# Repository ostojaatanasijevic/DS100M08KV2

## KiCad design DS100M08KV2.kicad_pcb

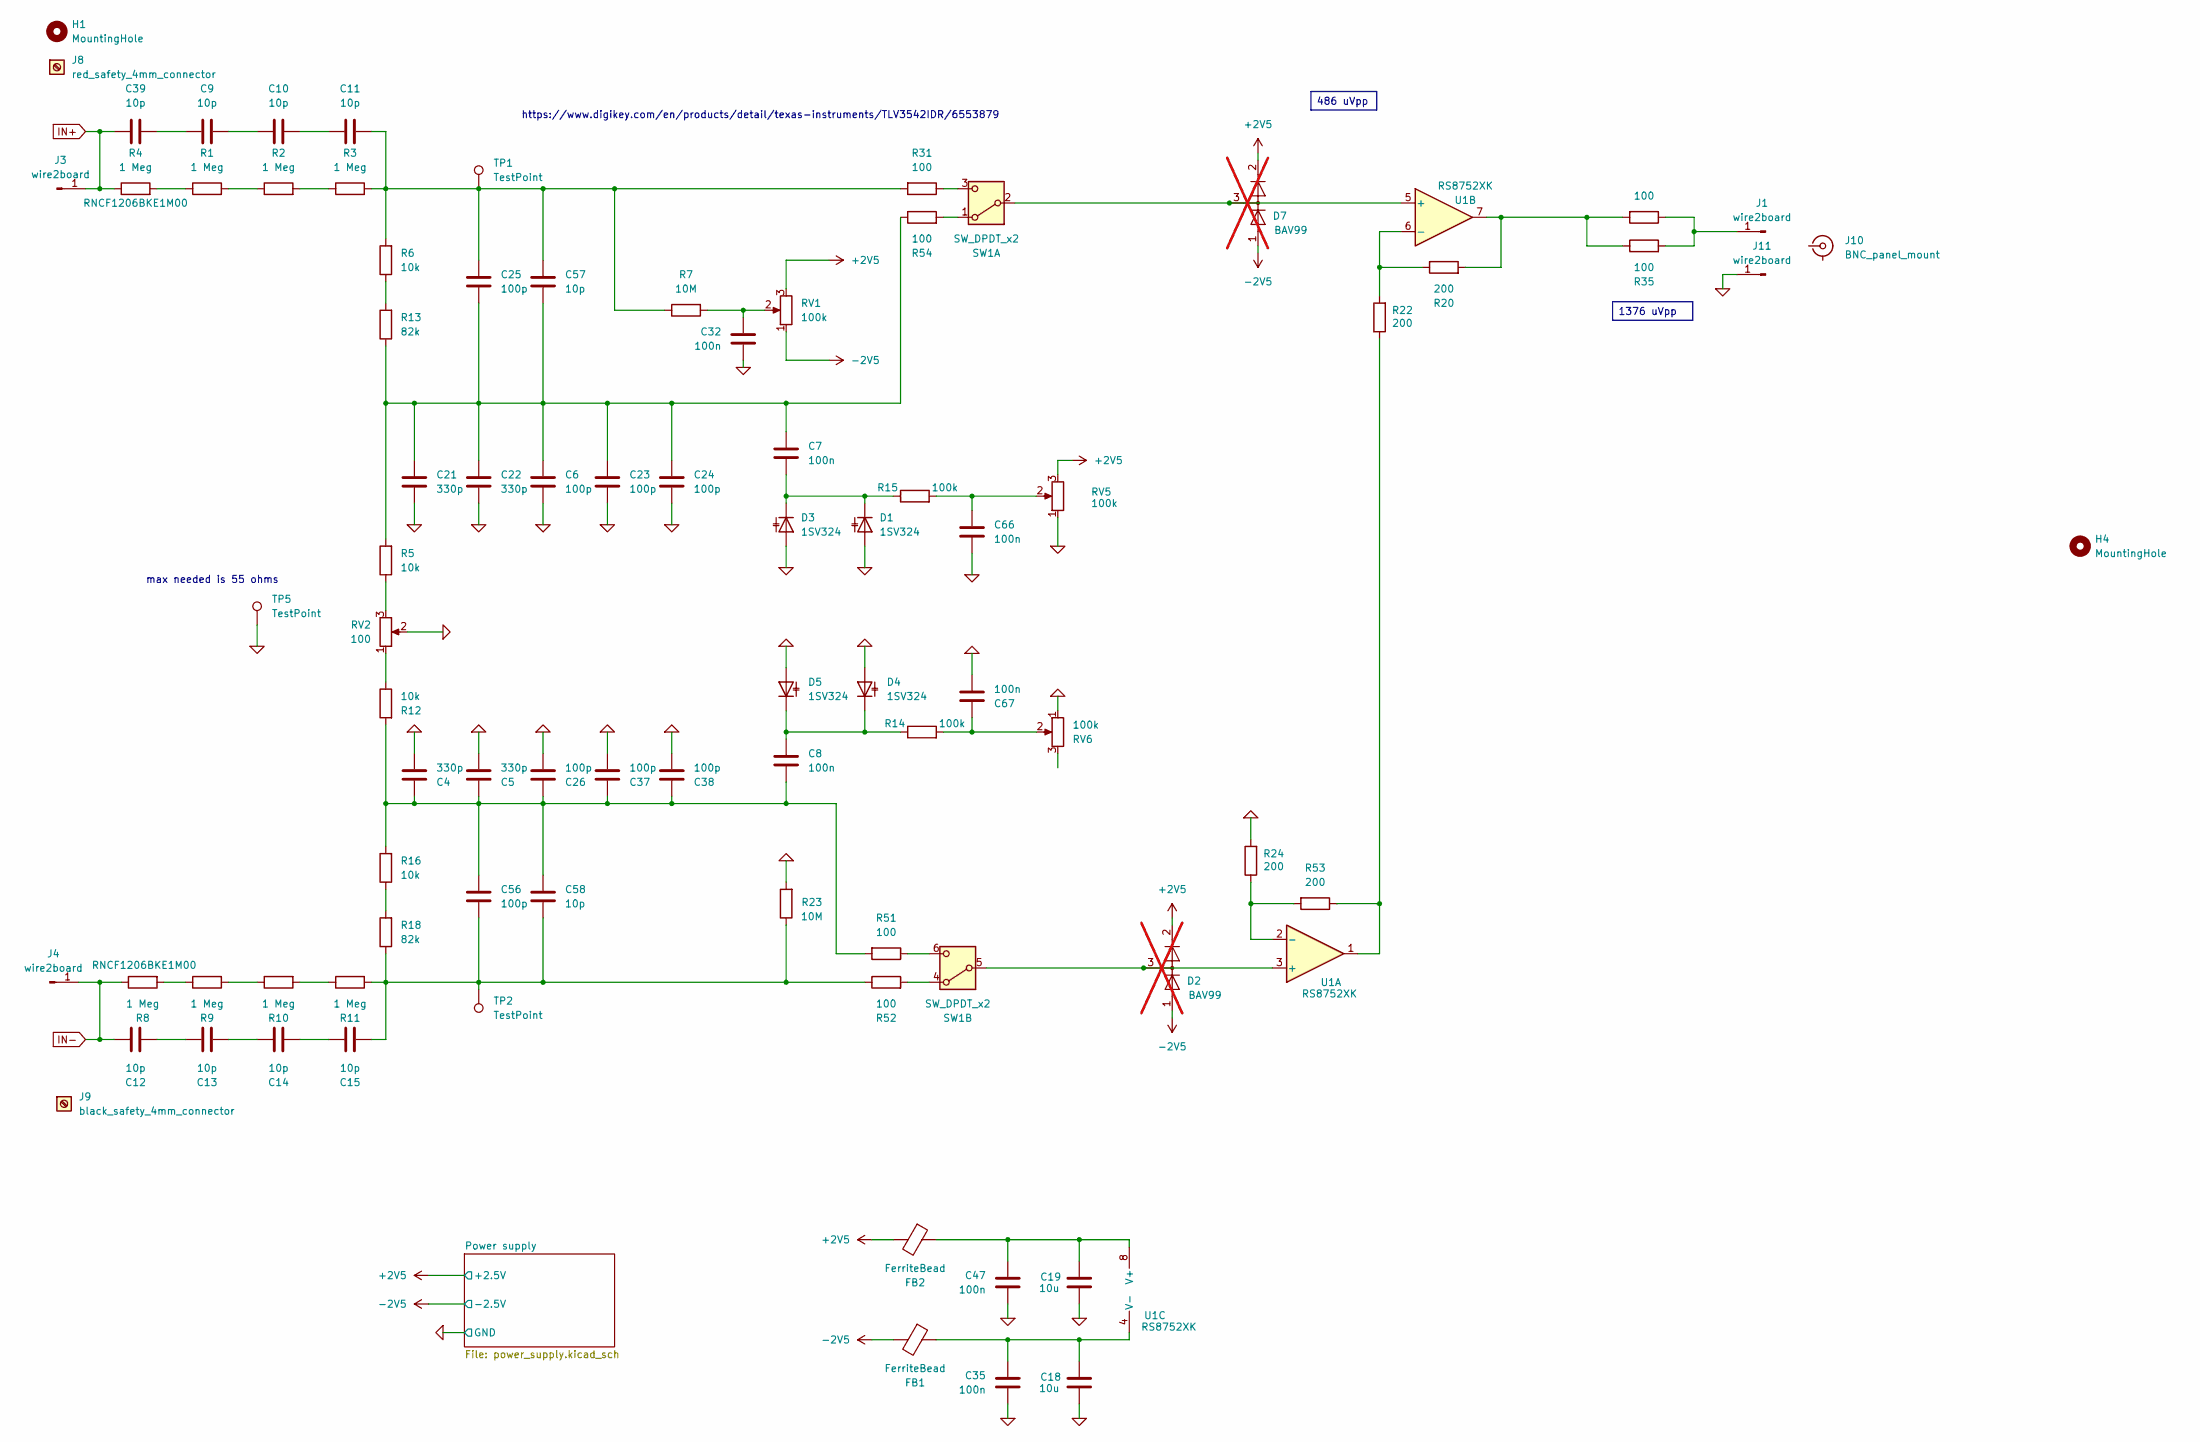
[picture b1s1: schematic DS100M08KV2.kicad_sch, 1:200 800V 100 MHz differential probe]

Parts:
C4, C5, C21, C22: 330p; R_0603_1608Metric_Pad0.98x0.95mm_HandSolder; LCSC C1664
C6, C23, C24, C25, C26, C37, C38, C56: 100p; R_0603_1608Metric_Pad0.98x0.95mm_HandSolder; LCSC C14858
C7, C8, C32, C35, C47, C66, C67: 100n; C_0603_1608Metric_Pad1.08x0.95mm_HandSolder; LCSC C14663
C9, C10, C11, C12, C13, C14, C15, C39: 10p; R_1206_3216Metric_Pad1.30x1.75mm_HandSolder
C18, C19: 10u; C_0603_1608Metric_Pad1.08x0.95mm_HandSolder; LCSC C96446
C57, C58: 10p; R_0603_1608Metric_Pad0.98x0.95mm_HandSolder; LCSC C1634
D1, D3, D4, D5: 1SV324; D_SOD-323_HandSoldering
D2, D7: BAV99; SOT-23; LCSC C2500; not fitted
FB1, FB2: FerriteBead; L_0603_1608Metric_Pad1.05x0.95mm_HandSolder
H1, H4: MountingHole; M3_with_screw
J1, J3, J4, J11: wire2board; SolderWire-0.25sqmm_1x01_D0.65mm_OD1.7mm
J8: red_safety_4mm_connector; black_safety_4mm_connector
J9: black_safety_4mm_connector
J10: BNC_panel_mount
R1, R2, R3, R9, R10, R11: 1 Meg; R_1206_3216Metric_Pad1.30x1.75mm_HandSolder
R4, R8: 1 Meg; R_1206_3216Metric_Pad1.30x1.75mm_HandSolder; Partnumber RNCF1206BKE1M00
R5, R6, R12, R16: 10k; R_0603_1608Metric_Pad0.98x0.95mm_HandSolder
R7, R23: 10M; R_0603_1608Metric_Pad0.98x0.95mm_HandSolder; LCSC C7250
R13, R18: 82k; R_0603_1608Metric_Pad0.98x0.95mm_HandSolder
R14, R15: 100k; R_0603_1608Metric_Pad0.98x0.95mm_HandSolder; LCSC C25803
R17, R31, R35, R51, R52, R54: 100; R_0603_1608Metric_Pad0.98x0.95mm_HandSolder; LCSC C22775
R20, R22, R24, R53: 200; R_0603_1608Metric_Pad0.98x0.95mm_HandSolder
RV1, RV5, RV6: 100k; Potentiometer_Bourns_3296W_Vertical
RV2: 100; Potentiometer_Bourns_3296W_Vertical
SW1: SW_DPDT_x2; DPDT_bigger
TP1, TP2, TP5: TestPoint; TestPoint_Pad_D2.0mm
U1: RS8752XK; SOIC-8_3.9x4.9mm_P1.27mm; LCSC RS8752XK

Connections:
0: C4.2, C5.2, C6.1, C18.2, C19.2, C21.2, C22.2, C23.1, C24.1, C26.1, C32.1, C35.1, C37.1, C38.1, C47.1, C66.1, C67.1, D1.2 (A), D3.2 (A), D4.2 (A), D5.2 (A), J11.1, R23.2, R24.2, RV2.2, RV5.1, RV6.1, TP5.1; also elsewhere on the board
+2V5: D2.2 (A), D7.2 (A), FB2.2, RV1.3, RV5.3; also elsewhere on the board
-2V5: D2.1 (K), D7.1 (K), FB1.2, RV1.1; also elsewhere on the board
IN+: C39.2, J3.1, R4.1
IN-: C12.2, J4.1, R8.1
unnamed: C10.1, C11.2
unnamed: C9.1, C10.2
unnamed: C11.1, C25.2, C57.2, R3.2, R6.2, R7.1, R31.2, TP1.1
unnamed: C12.1, C13.2
unnamed: C13.1, C14.2
unnamed: C14.1, C15.2
unnamed: C15.1, C56.1, C58.1, R11.2, R18.1, R23.1, R52.1, TP2.1
unnamed: C6.2, C7.2, C21.1, C22.1, C23.2, C24.2, C25.1, C57.1, R5.2, R13.1, R54.1
unnamed: C4.1, C5.1, C8.1, C26.2, C37.2, C38.2, C56.2, C58.2, R12.2, R16.2, R51.2
unnamed: C32.2, R7.2, RV1.2
unnamed: C9.2, C39.1
unnamed: C66.2, R15.2, RV5.2
unnamed: C67.2, R14.2, RV6.2
unnamed: C7.1, D1.1 (K), D3.1 (K), R15.1
unnamed: C8.2, D4.1 (K), D5.1 (K), R14.1
unnamed: J1.1, R17.1, R35.2
unnamed: R1.1, R4.2
unnamed: R1.2, R2.1
unnamed: R2.2, R3.1
unnamed: R5.1, RV2.3
unnamed: R8.2, R9.1
unnamed: R9.2, R10.1
unnamed: R10.2, R11.1
unnamed: R12.1, RV2.1
unnamed: R6.1, R13.2
unnamed: R16.1, R18.2
unnamed: R17.2, R20.2, R35.1, U1.7
unnamed: R22.1, R53.1, U1.1
unnamed: R54.2, SW1.1 (A)
unnamed: D7.3 (K), SW1.2 (B), U1.5 (+)
unnamed: R31.1, SW1.3 (C)
unnamed: R52.2, SW1.4 (A)
unnamed: D2.3 (K), SW1.5 (B), U1.3 (+)
unnamed: R51.1, SW1.6 (C)
unnamed: R24.1, R53.2, U1.2 (-)
unnamed: R20.1, R22.2, U1.6 (-)
unnamed: C19.1, C47.2, FB2.1, U1.8 (V+)
unnamed: C18.1, C35.2, FB1.1, U1.4 (V-)

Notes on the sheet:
https://www.digikey.com/en/products/detail/texas-instruments/TLV3542IDR/6553879
max needed is 55 ohms
1376 uVpp
486 uVpp

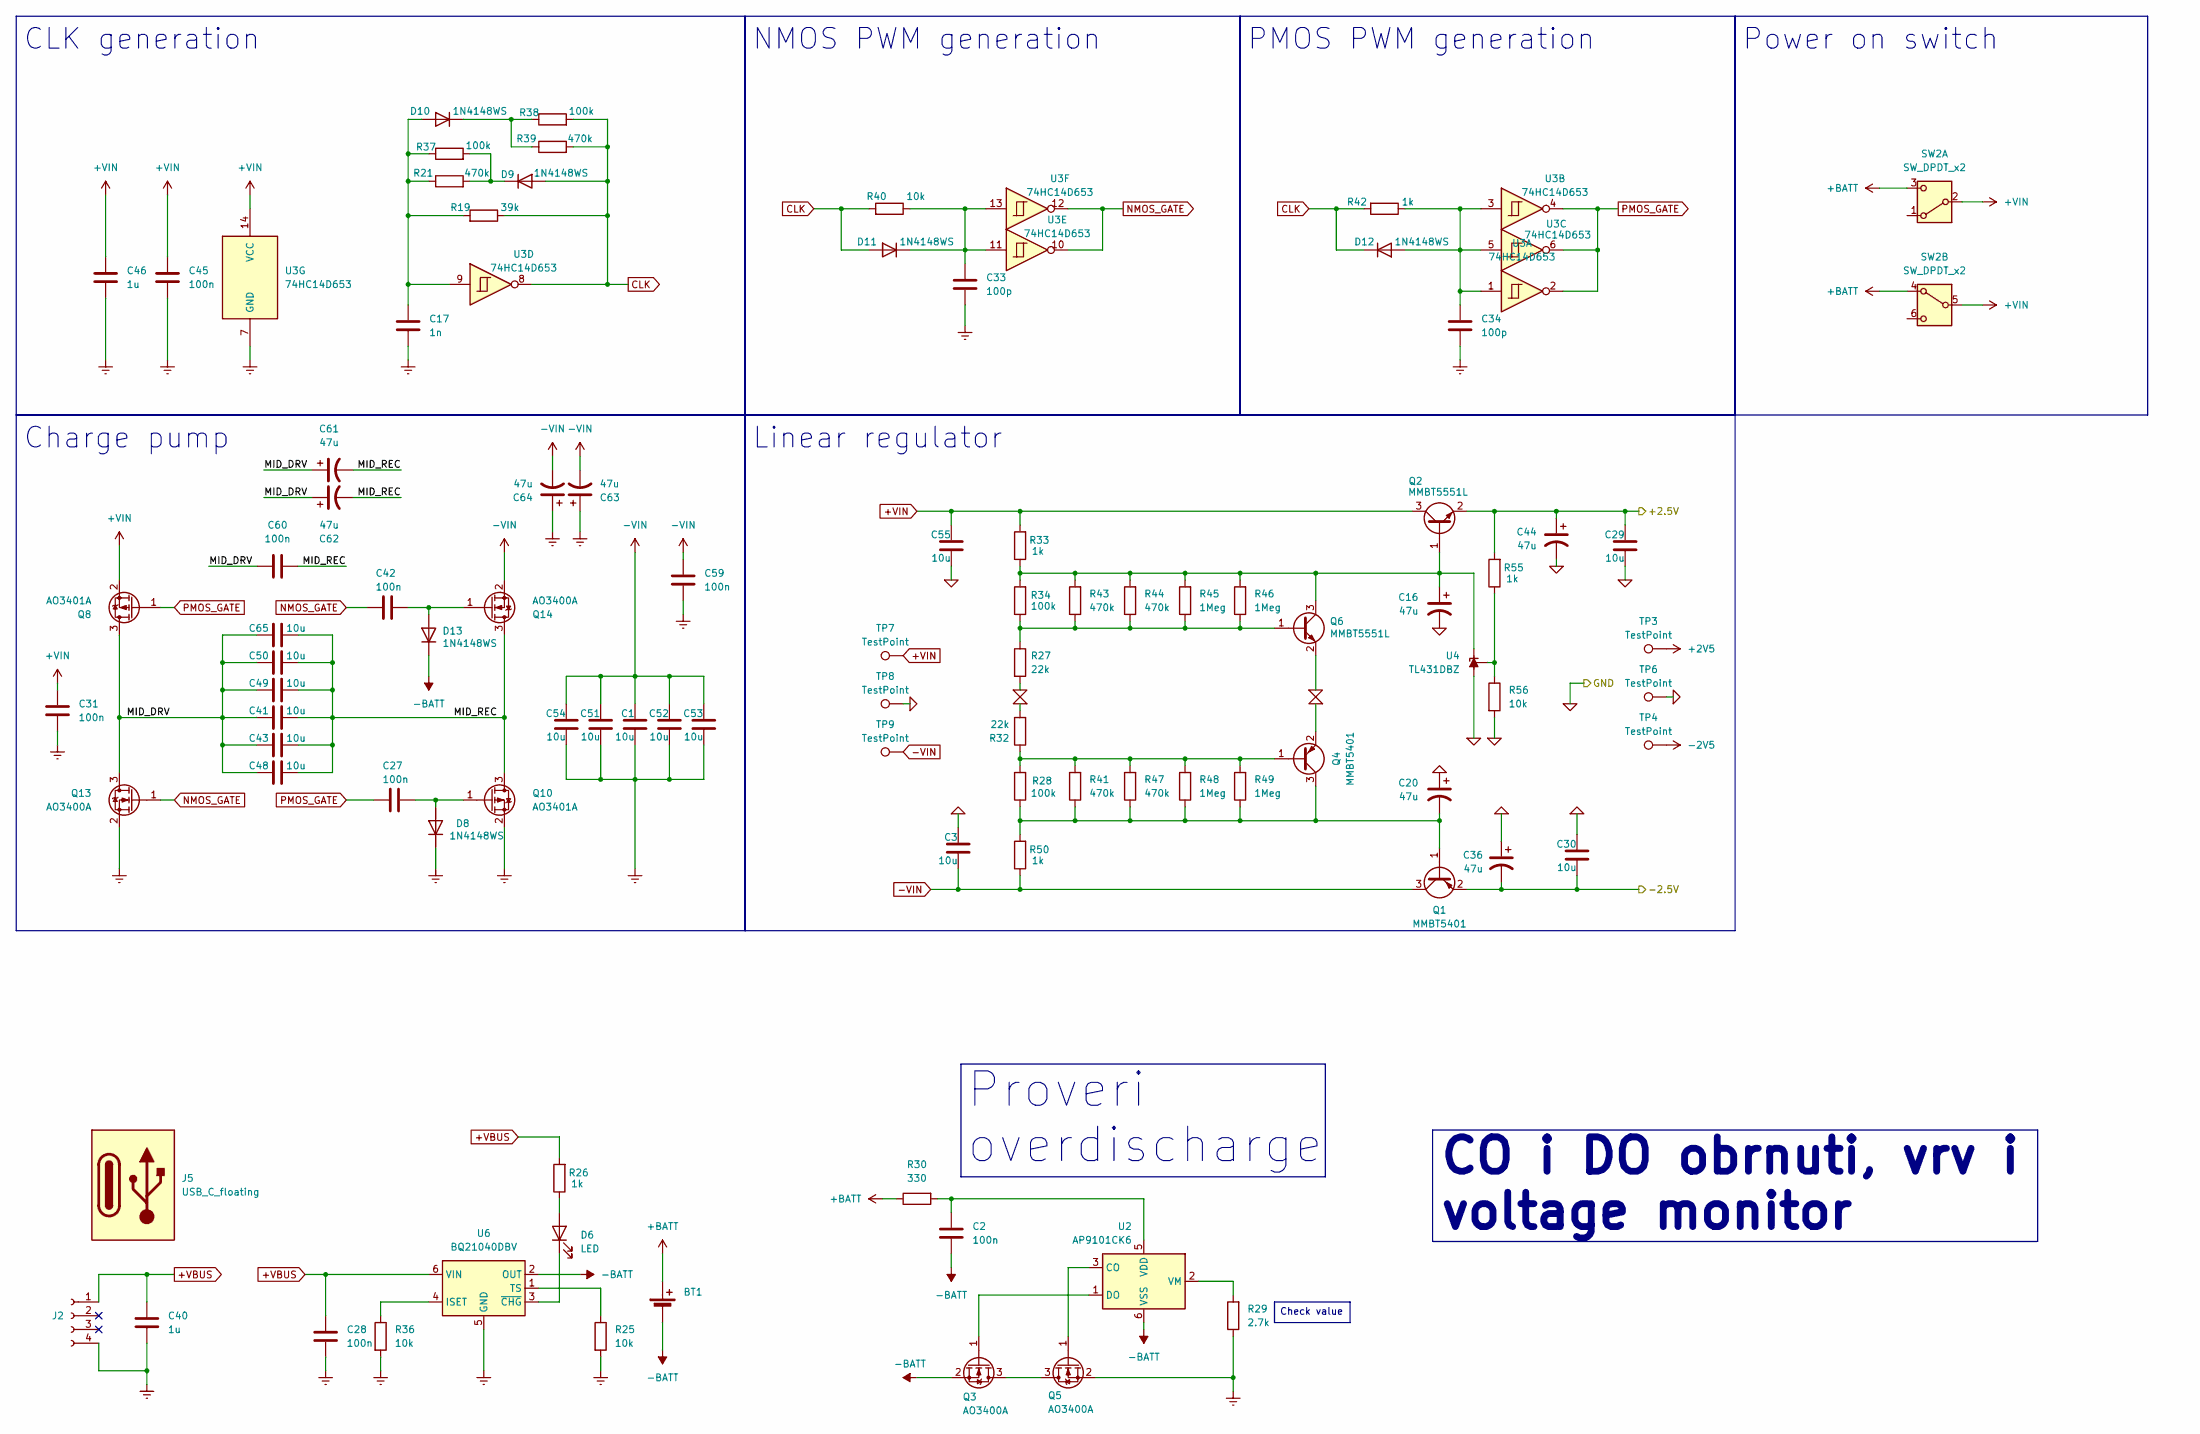
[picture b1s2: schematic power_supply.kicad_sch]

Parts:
BT1: Battery_Cell; battery_holder
C1, C3, C29, C30, C41, C43, C48, C49, C50, C51, C52, C53, C54, C55, C65: 10u; R_0805_2012Metric_Pad1.20x1.40mm_HandSolder; Voltage 25V; LCSC C15850
C2, C27, C28, C31, C42, C45, C59, C60: 100n; C_0603_1608Metric_Pad1.08x0.95mm_HandSolder; LCSC C14663
C16, C20, C36, C44, C61, C62, C63, C64: 47u; CP_Radial_D5.0mm_P2.00mm
C17: 1n; C_0603_1608Metric_Pad1.08x0.95mm_HandSolder; LCSC C1588
C33, C34: 100p; C_0603_1608Metric_Pad1.08x0.95mm_HandSolder; LCSC C14858
C40, C46: 1u; C_0603_1608Metric_Pad1.08x0.95mm_HandSolder; LCSC C15849
D6: LED; LED_D3.0mm_FlatTop
D8, D9, D10, D11, D12, D13: 1N4148WS; D_SOD-323; LCSC C2128
J2: Conn_01x04_Socket; JST_PH_B4B-PH-K_1x04_P2.00mm_Vertical
J5: USB_C_floating
Q1, Q4: MMBT5401; SOT-23; LCSC C8326
Q2, Q6: MMBT5551L; SOT-23; LCSC C2145
Q3, Q5, Q13, Q14: AO3400A; SOT-23; LCSC C20917
Q8, Q10: AO3401A; SOT-23; LCSC C15127
R19: 39k; R_0603_1608Metric_Pad0.98x0.95mm_HandSolder; LCSC C23153
R21, R39, R41, R43, R44, R47: 470k; R_0603_1608Metric_Pad0.98x0.95mm_HandSolder; LCSC C23178
R25, R36, R40, R56: 10k; R_0603_1608Metric_Pad0.98x0.95mm_HandSolder; LCSC C25804
R26, R33, R42, R50, R55: 1k; R_0603_1608Metric_Pad0.98x0.95mm_HandSolder; LCSC C21190
R27, R32: 22k; R_0603_1608Metric_Pad0.98x0.95mm_HandSolder; LCSC C31850
R28, R34, R37, R38: 100k; R_0603_1608Metric_Pad0.98x0.95mm_HandSolder; LCSC C25803
R29: 2.7k; R_0603_1608Metric_Pad0.98x0.95mm_HandSolder; LCSC C13167
R30: 330; R_0603_1608Metric_Pad0.98x0.95mm_HandSolder; LCSC C23138
R45, R46, R48, R49: 1Meg; R_0603_1608Metric_Pad0.98x0.95mm_HandSolder; LCSC C22935
SW2: SW_DPDT_x2; DPDT_bigger
TP3, TP4, TP6, TP7, TP8, TP9: TestPoint; TestPoint_Pad_D2.0mm
U2: AP9101CK6; SOT-23-6
U3: 74HC14D653; SOIC-14_3.9x8.7mm_P1.27mm; LCSC C5605
U4: TL431DBZ; SOT-23; LCSC C3113
U6: BQ21040DBV; SOT-23-6

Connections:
0: C3.2, C16.2, C20.1, C29.1, C30.2, C36.1, C44.2, C55.1, Q4.2 (E), Q6.2 (E), R27.2, R32.2, R56.2, TP6.1, TP8.1, U4.3 (A); also elsewhere on the board
+2V5: C29.2, C44.1, Q2.2 (E), R55.2, TP3.1; also elsewhere on the board
+BATT: BT1.1 (+), R30.1, SW2.3 (C), SW2.4 (A)
+VBUS: C28.2, C40.2, J2.1, R26.2, U6.6 (VIN)
+VIN: C31.2, C45.2, C46.2, C55.2, Q2.3 (C), Q8.2 (S), R33.2, SW2.2 (B), SW2.5 (B), TP7.1, U3.14 (VCC)
-2V5: C30.1, C36.2, Q1.2 (E), TP4.1; also elsewhere on the board
-BATT: BT1.2 (-), C2.1, D13.1 (K), Q3.2 (S), U2.6 (VSS), U6.2 (OUT)
-VIN: C1.2, C3.1, C51.2, C52.2, C53.2, C54.2, C59.2, C63.2, C64.2, Q1.3 (C), Q14.2 (S), R50.1, TP9.1
/Power supply/MID_DRV: C41.1, C43.1, C48.1, C49.1, C50.1, C60.2, C61.1, C62.1, C65.1, Q8.3 (D), Q13.3 (D)
/Power supply/MID_REC: C41.2, C43.2, C48.2, C49.2, C50.2, C60.1, C61.2, C62.2, C65.2, Q10.3 (D), Q14.3 (D)
CLK: D9.2 (A), D11.2 (A), D12.1 (K), R19.1, R38.2, R39.2, R40.2, R42.2, U3.8
Earth: C1.1, C17.1, C28.1, C31.1, C33.1, C34.1, C40.1, C45.1, C46.1, C51.1, C52.1, C53.1, C54.1, C59.1, C63.1, C64.1, D8.1 (K), J2.4, Q5.2 (S), Q10.2 (S), Q13.2 (S), R25.2, R29.1, R36.2, U3.7 (GND), U6.5 (GND)
NMOS_GATE: C42.1, Q13.1 (G), U3.10, U3.12
unnamed: D6.2 (A), R26.1
unnamed: D6.1 (K), U6.3 (~CHG)
unnamed: C27.2, D8.2 (A), Q10.1 (G)
unnamed: D9.1 (K), R21.2, R37.2
unnamed: C17.2, D10.2 (A), R19.2, R21.1, R37.1, U3.9
unnamed: D10.1 (K), R38.1, R39.1
unnamed: C33.2, D11.1 (K), R40.1, U3.11, U3.13
unnamed: C34.2, D12.2 (A), R42.1, U3.1, U3.3, U3.5
unnamed: C42.2, D13.2 (A), Q14.1 (G)
unnamed: C20.2, Q1.1 (B), Q4.3 (C), R28.1, R41.1, R47.1, R48.1, R49.1, R50.2
unnamed: C16.1, Q2.1 (B), Q6.3 (C), R33.1, R34.2, R43.2, R44.2, R45.2, R46.2, U4.1 (K)
unnamed: Q3.3 (D), Q5.3 (D)
unnamed: Q3.1 (G), U2.1 (DO)
unnamed: Q4.1 (B), R28.2, R32.1, R41.2, R47.2, R48.2, R49.2
unnamed: Q5.1 (G), U2.3 (CO)
unnamed: Q6.1 (B), R27.1, R34.1, R43.1, R44.1, R45.1, R46.1
unnamed: C2.2, R30.2, U2.5 (VDD)
unnamed: R29.2, U2.2 (VM)
unnamed: R55.1, R56.1, U4.2 (REF)
unnamed: R36.1, U6.4 (ISET)
unnamed: R25.1, U6.1 (TS)
PMOS_GATE: C27.1, Q8.1 (G), U3.2, U3.4, U3.6

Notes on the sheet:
Charge pump
CLK generation
Power on switch
Linear regulator
PMOS PWM generation
NMOS PWM generation
Proveri overdischarge
Check value
CO i DO obrnuti, vrv i voltage monitor

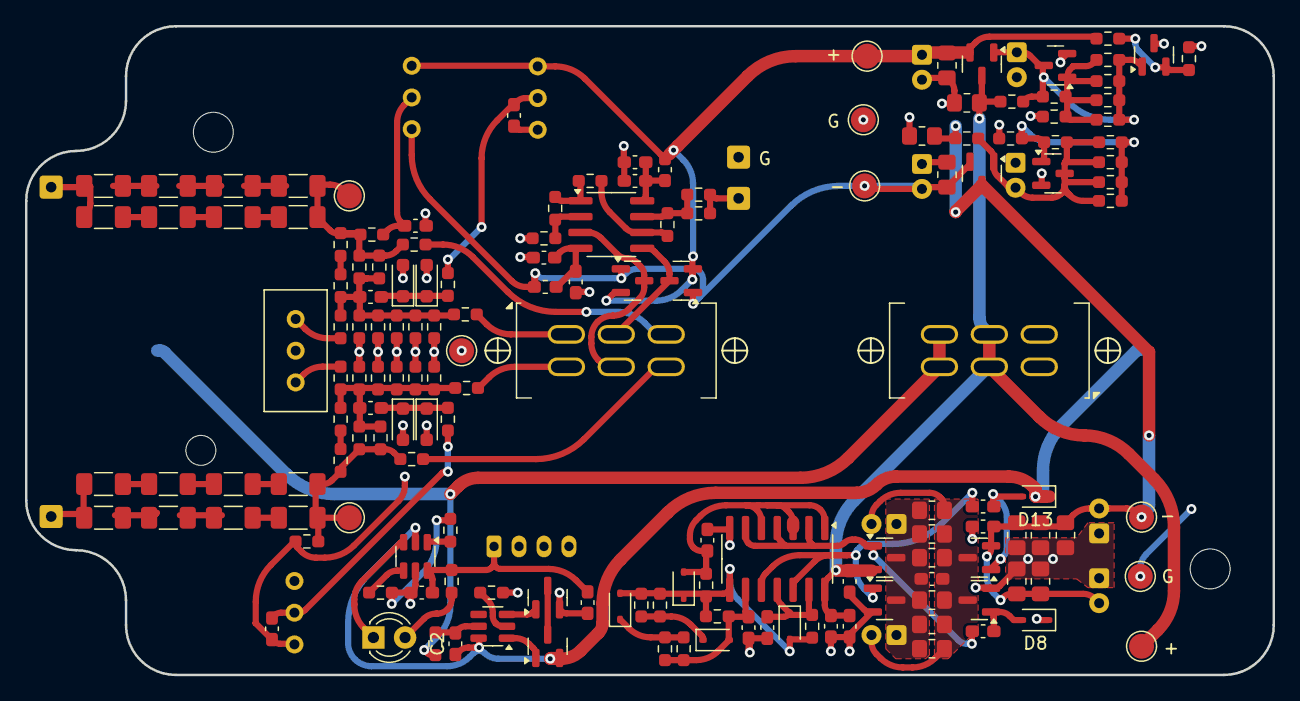
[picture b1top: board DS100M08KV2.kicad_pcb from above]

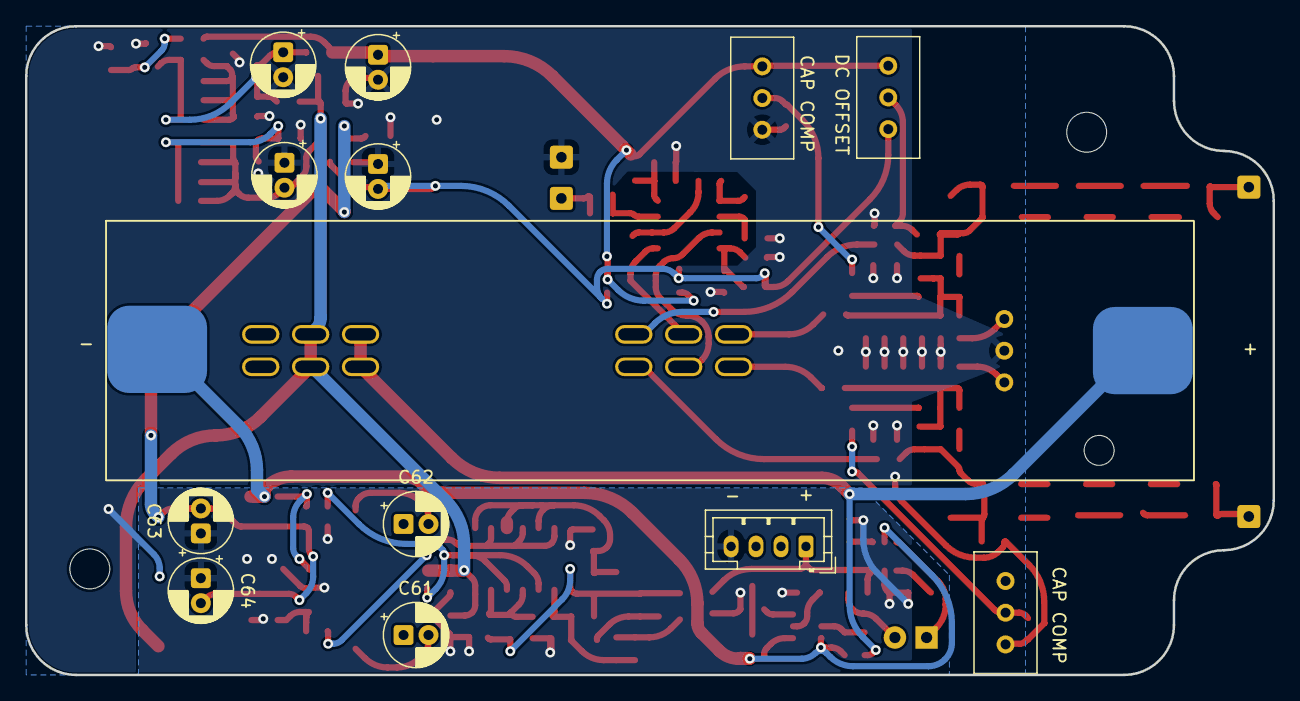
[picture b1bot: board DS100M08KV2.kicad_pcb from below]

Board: 2 copper layers, 100.0 x 52.0 mm, 180 parts (19 on the bottom side), 75 nets.

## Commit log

2025-10-23 Init
2025-10-24 new osc.
2025-10-25 New sims, added switcher to PCB.
2025-10-27 Sims, schem.
2025-10-27 Layout.
2025-10-27 Layout
2025-10-27 Placement done.
2025-10-27 Switcher done.
2025-10-28 Lin Reg.
2025-10-28 Amp.
2025-10-28 Almost done.
2025-10-28 Skoro gotovo Skoro gotovo
2025-11-04 tiny update.
